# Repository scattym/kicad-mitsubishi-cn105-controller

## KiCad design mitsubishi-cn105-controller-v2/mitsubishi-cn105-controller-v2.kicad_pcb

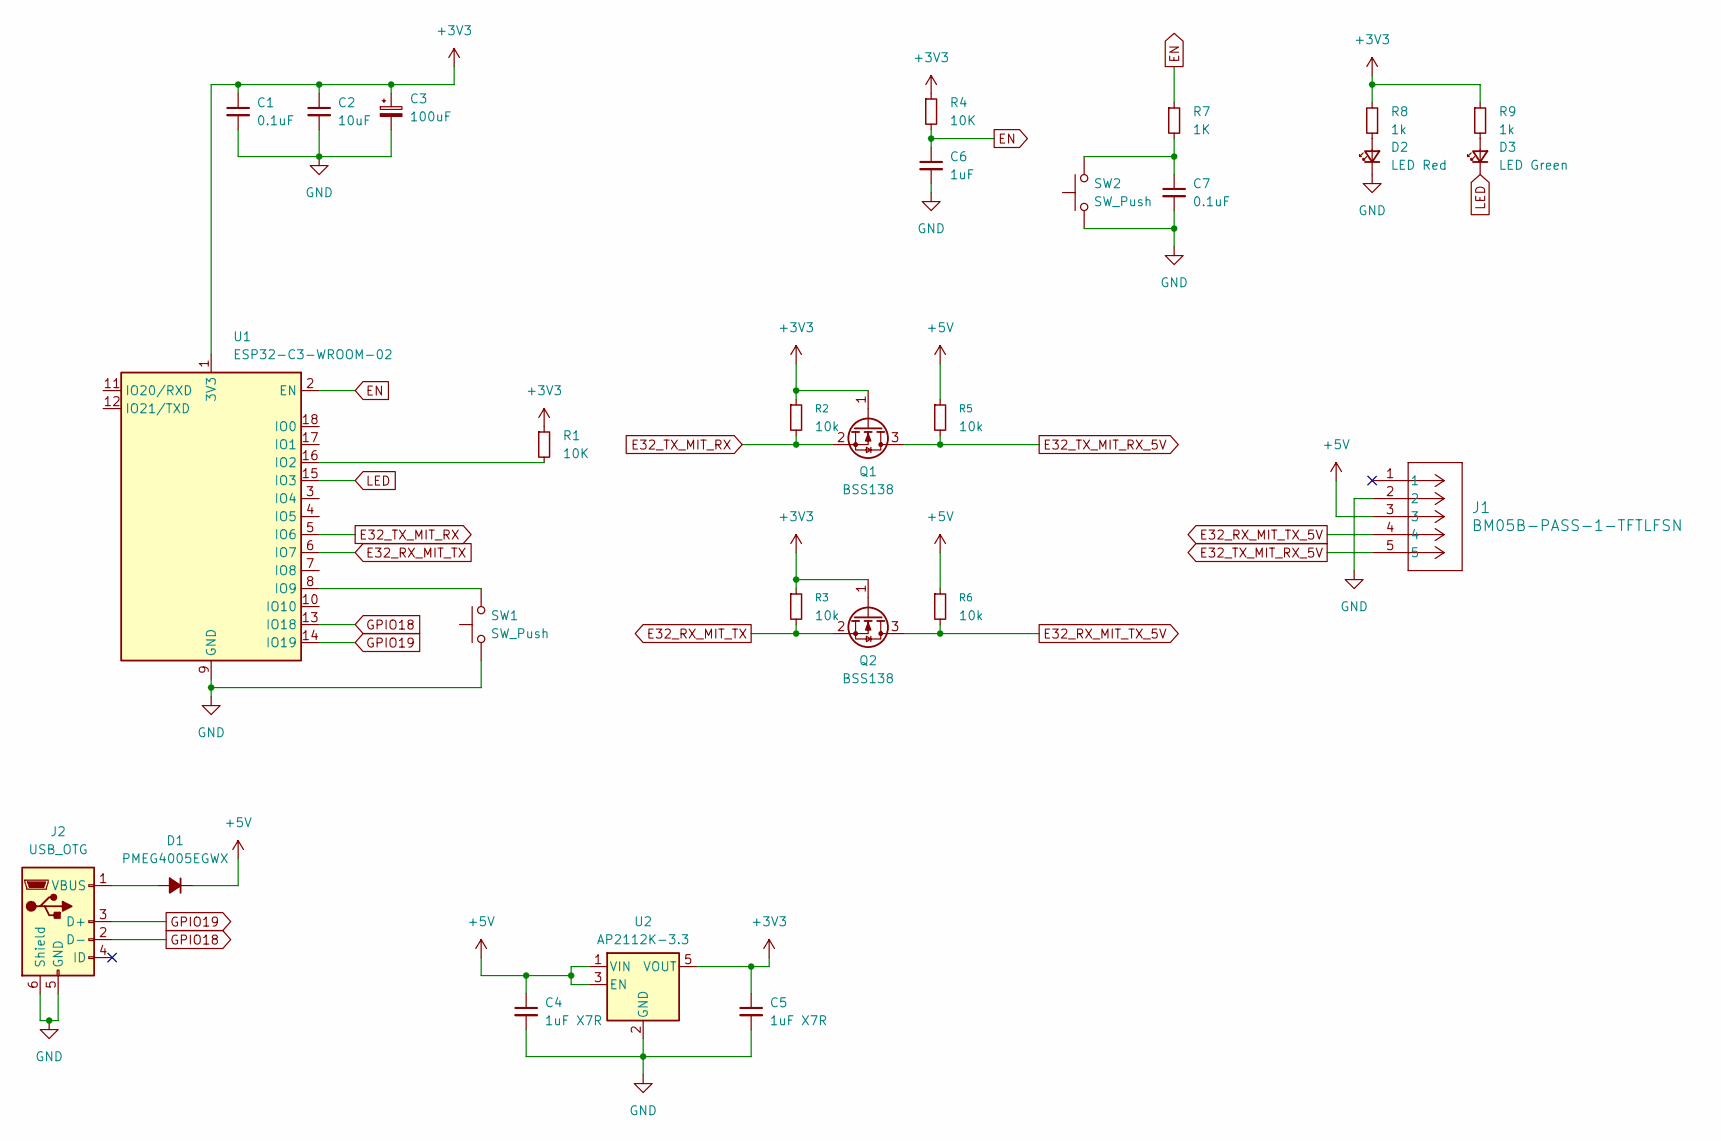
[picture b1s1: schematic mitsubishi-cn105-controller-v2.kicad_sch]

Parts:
C1: 0.1uF; C_0805_2012Metric
C2: 10uF; C_0805_2012Metric
C3: 100uF; CP_EIA-3528-12_Kemet-T
C4, C5: 1uF X7R; C_0805_2012Metric
C6: 1uF; C_0603_1608Metric
C7: 0.1uF; C_0603_1608Metric
D1: PMEG4005EGWX; D_SOD-123
D2: LED Red; LED_0603_1608Metric
D3: LED Green; LED_0603_1608Metric
J1: BM05B-PASS-1-TFTLFSN; CONN_BM05B-PASS-1_JST
J2: USB_OTG; USB_Micro-B_Molex-105017-0001
Q1, Q2: BSS138; SOT-23
R1, R4: 10K; R_0603_1608Metric
R2, R3, R5, R6: 10k; R_0603_1608Metric
R7: 1K; R_0603_1608Metric
R8, R9: 1k; R_0603_1608Metric
SW1, SW2: SW_Push; SW_SPST_CK_RS282G05A3
U1: ESP32-C3-WROOM-02
U2: AP2112K-3.3; SOT-23-5

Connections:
+3V3: C1.1, C2.1, C3.1, C5.1, Q1.1 (G), Q2.1 (G), R1.1, R2.1, R3.1, R4.1, R8.2, R9.1, U1.1 (3V3), U2.5 (VOUT)
+5V: C4.1, D1.1 (K), J1.3, R5.1, R6.1, U2.1 (VIN), U2.3 (EN)
E32_RX_MIT_TX: Q2.2 (S), R3.2, U1.6 (IO7)
E32_RX_MIT_TX_5V: J1.4, Q2.3 (D), R6.2
E32_TX_MIT_RX: Q1.2 (S), R2.2, U1.5 (IO6)
E32_TX_MIT_RX_5V: J1.5, Q1.3 (D), R5.2
EN: C6.1, R4.2, R7.1, U1.2 (EN)
GND: C1.2, C2.2, C3.2, C4.2, C5.2, C6.2, C7.2, D2.1 (K), J1.2, J2.5 (GND), J2.6 (Shield), SW1.1, SW2.1, U1.9 (GND), U1.19 (GND), U2.2 (GND)
GPIO18: J2.2 (D-), U1.13 (IO18)
GPIO19: J2.3 (D+), U1.14 (IO19)
LED: D3.1 (K), U1.15 (IO3)
unnamed: C7.1, R7.2, SW2.2
unnamed: D1.2 (A), J2.1 (VBUS)
unnamed: D2.2 (A), R8.1
unnamed: D3.2 (A), R9.2
unnamed: R1.2, U1.16 (IO2)
unnamed: SW1.2, U1.8 (IO9)

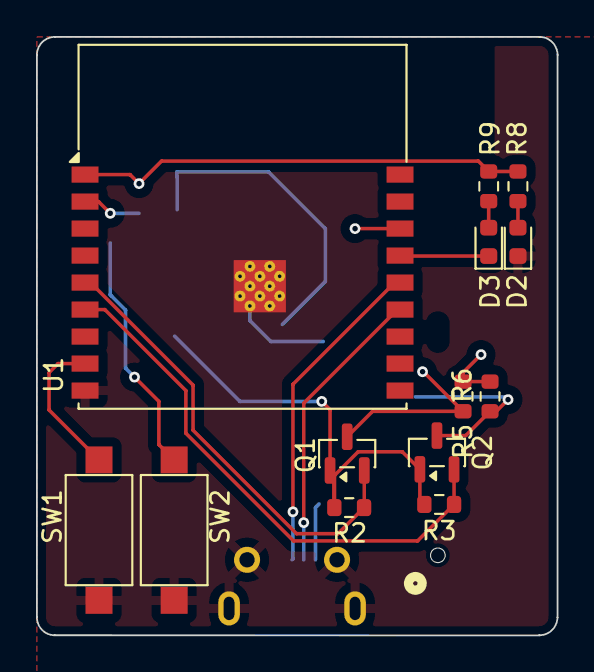
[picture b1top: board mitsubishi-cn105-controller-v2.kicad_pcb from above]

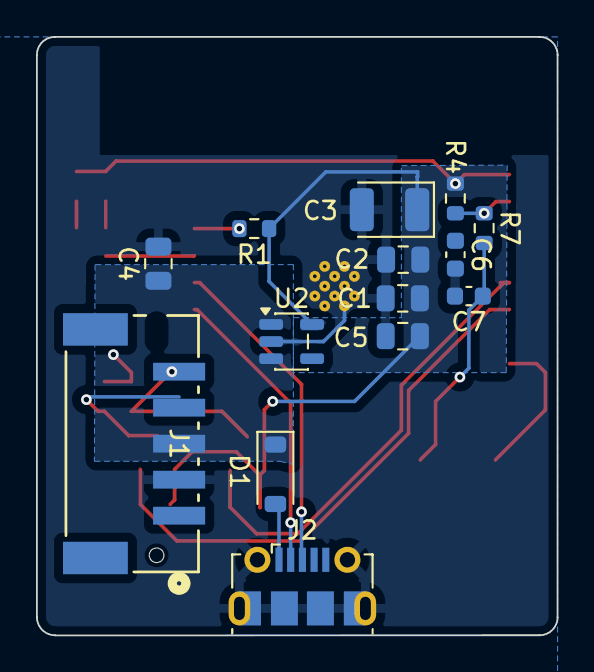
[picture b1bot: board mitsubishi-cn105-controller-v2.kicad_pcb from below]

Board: 2 copper layers, 28.9 x 33.3 mm, 27 parts (14 on the bottom side), 17 nets.

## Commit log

2026-06-14 Initial import of the mitsubishi air con controller
2026-06-14 Start on pcb design
2026-06-14 Very quick basic board layout
2026-06-14 Close to v1 complete.
2026-06-19 Adding SMD connector version of the board.
